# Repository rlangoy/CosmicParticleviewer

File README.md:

# Cosmic particle readout system overview

## Readout Hardware

Schematics and PCB layout is found inn the kicadv6 folder   \
Design files for the cover is found in the the CAD foldder 

## Project Content 
### alpideInterface
Microcontroller firmware source for [Arduino IDE 2.x](https://github.com/arduino/arduino-ide) \
&nbsp; parses JSON command and sends it to the ALPIDES \
&nbsp; More Info Available in the [README](/ArduinoV2/README.md) 

### KicadV6  
PCB Design files for [Kicadv6] (https://www.kicad.org/) \
&nbsp; More Info Available in the [README](/KicadV6/README.md) 

### CAD  
CAD Design files for PCB cover [Freecad v0.21] (https://www.freecad.org/) \
&nbsp; More Info Available in the [README](/CAD/README.md) 

### Python
Python ver 3.x Library and Examples for reading/accessing the Alpide OB Modules \
&nbsp; More Info Available in the [README](/Python/README.md)

### InfluxDB
InfluxDB 2.x Python3 script for inserting ALPIDE data into the daatabase and Script for building the Dashboard \
&nbsp; More Info Available in the [README](/InfluxDB/README.md)

## Getting started
- Transfer .u2f file to the RPI Pico
- Modify Serial port in plotAplideHitmap.py
  - Run [plotAplideHitmap.py](/Python/plotAplideHitmap.py) (python3 plotAplideHitmap.py )

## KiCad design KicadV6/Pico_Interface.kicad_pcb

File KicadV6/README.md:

# Kicad Files for Raspberry Pico (RP2040) interface to Outer Barrel Module
## PCB Layout. 
 
\
The Mounting holes is designed for 4M Screws \

## RP2040 Pinout 

## +3,3V Source Selection

## Fabrication
The PCB can be fabricated by uploading the gerber files (KicadV6\gerber\Pico_Interface.zip)  to a [PCB manufacurer](https://jlcpcb.com/) 

## Bil of Materials (BOM)

| Quantity | Reference(s) | Prod no             | Farnell order no | Description                                                |   |
|----------|--------------|---------------------|------------------|------------------------------------------------------------|---|
| 1        | C1           | T491A106K016AT      | 1457414          | T491A106K016AT CAP, 10µF, 16V, 10%, 1206, SMD              |   |
| 4        | J0-J3        | MC-254-12-00-ST-DIP | 2843528          | MC-254-12-00-ST-DIP CONNECTOR, HEADER, 12POS, 2ROW, 2.54MM |   |
| 1        | U2           | NCP1117ST33T3G      | 1652366          | NCP1117ST33T3G IC, LINEAR VOLTAGE REGULATOR                |   |
| 1        | U1           |                     |                  | Rasbperry Pi Pico                                          |   |

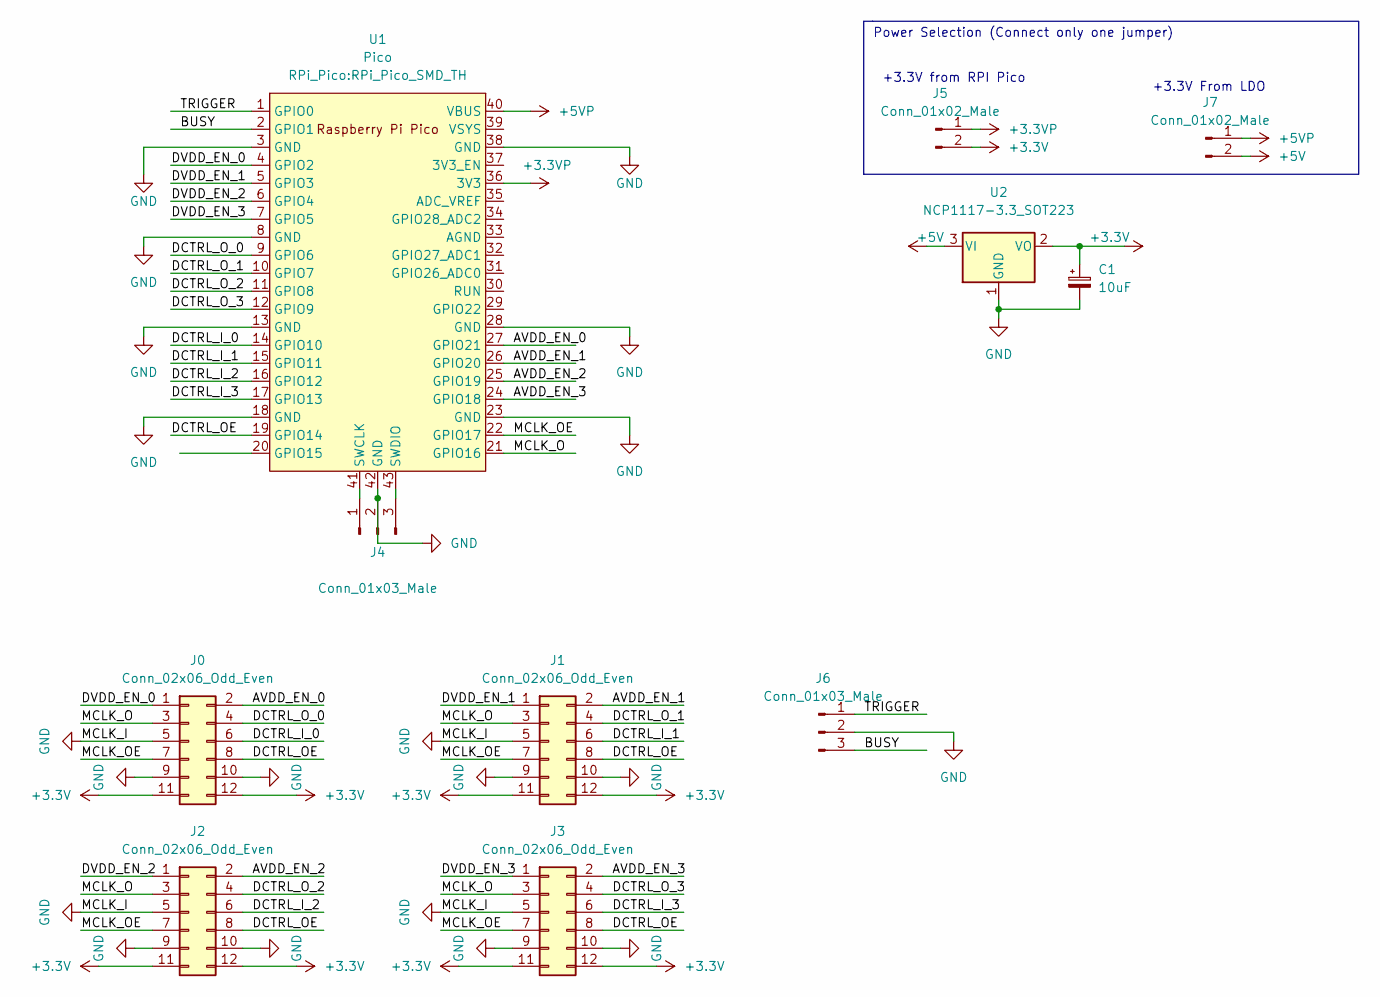
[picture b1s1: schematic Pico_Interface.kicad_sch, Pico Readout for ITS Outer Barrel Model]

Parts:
C1: 10uF; C_1206_3216Metric_Pad1.33x1.80mm_HandSolder
J0, J1, J2, J3: Conn_02x06_Odd_Even; IDC-Header_2x06_P2.54mm_Vertical
J4, J6: Conn_01x03_Male; PinHeader_1x03_P2.54mm_Vertical
J5, J7: Conn_01x02_Male; PinHeader_1x02_P2.54mm_Vertical
U1: Pico; RPi_Pico_SMD_TH
U2: NCP1117-3.3_SOT223; SOT-223-3_TabPin2

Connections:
+3.3V: C1.1, J0.11, J0.12, J1.11, J1.12, J2.11, J2.12, J3.11, J3.12, J5.2, U2.2 (VO)
+3.3VP: J5.1, U1.36 (3V3)
+5V: J7.2, U2.3 (VI)
+5VP: J7.1, U1.40 (VBUS)
/AVDD_EN_0: J0.2, U1.27 (GPIO21)
/AVDD_EN_1: J1.2, U1.26 (GPIO20)
/AVDD_EN_2: J2.2, U1.25 (GPIO19)
/AVDD_EN_3: J3.2, U1.24 (GPIO18)
/BUSY: J6.3, U1.2 (GPIO1)
/DCTRL_I_0: J0.6, U1.14 (GPIO10)
/DCTRL_I_1: J1.6, U1.15 (GPIO11)
/DCTRL_I_2: J2.6, U1.16 (GPIO12)
/DCTRL_I_3: J3.6, U1.17 (GPIO13)
/DCTRL_OE: J0.8, J1.8, J2.8, J3.8, U1.19 (GPIO14)
/DCTRL_O_0: J0.4, U1.9 (GPIO6)
/DCTRL_O_1: J1.4, U1.10 (GPIO7)
/DCTRL_O_2: J2.4, U1.11 (GPIO8)
/DCTRL_O_3: J3.4, U1.12 (GPIO9)
/DVDD_EN_0: J0.1, U1.4 (GPIO2)
/DVDD_EN_1: J1.1, U1.5 (GPIO3)
/DVDD_EN_2: J2.1, U1.6 (GPIO4)
/DVDD_EN_3: J3.1, U1.7 (GPIO5)
/MCLK_O: J0.3, J1.3, J2.3, J3.3, U1.21 (GPIO16)
/MCLK_OE: J0.7, J1.7, J2.7, J3.7, U1.22 (GPIO17)
/TRIGGER: J6.1, U1.1 (GPIO0)
GND: C1.2, J0.5, J0.9, J0.10, J1.5, J1.9, J1.10, J2.5, J2.9, J2.10, J3.5, J3.9, J3.10, J4.2, J6.2, U1.3 (GND), U1.8 (GND), U1.13 (GND), U1.18 (GND), U1.23 (GND), U1.28 (GND), U1.38 (GND), U1.42 (GND), U2.1 (GND)
unnamed: J4.1, U1.41 (SWCLK)
unnamed: J4.3, U1.43 (SWDIO)

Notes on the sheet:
Power Selection (Connect only one jumper)
+3.3V From LDO
+3.3V from RPI Pico

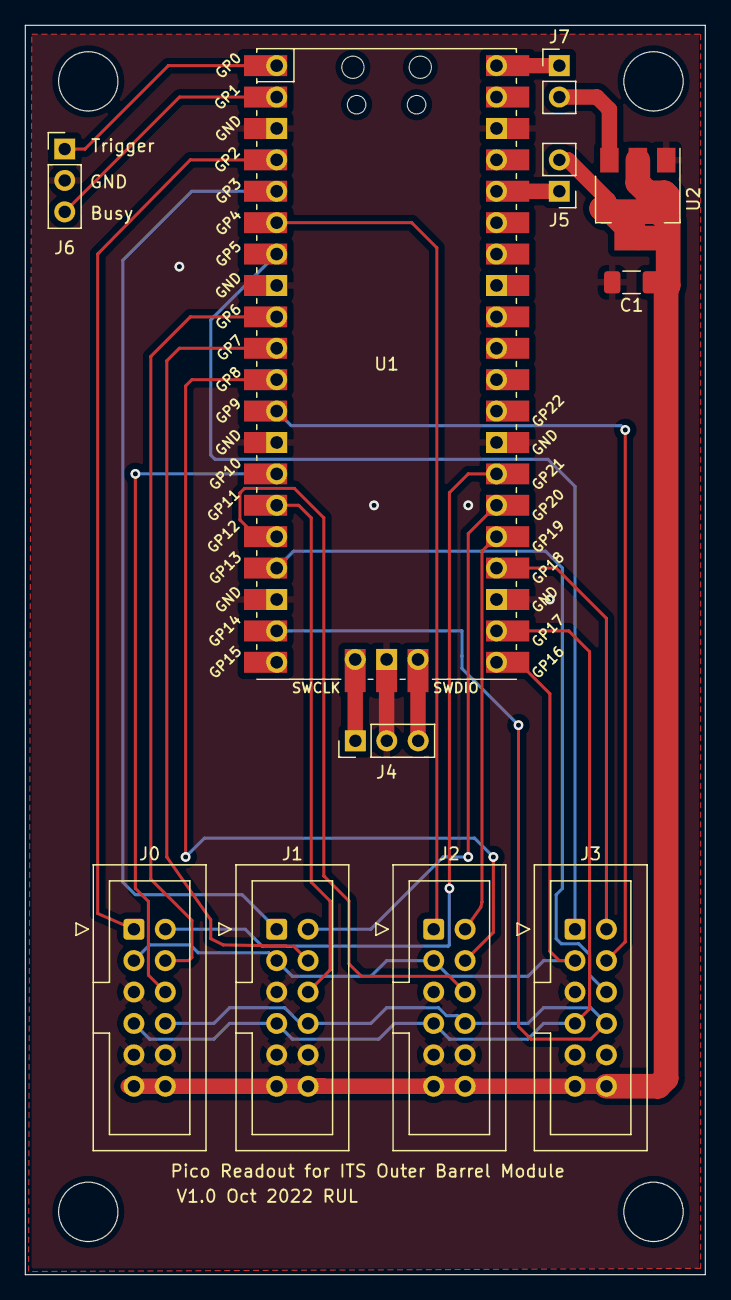
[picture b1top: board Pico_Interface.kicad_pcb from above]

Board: 2 copper layers, 55.0 x 101.1 mm, 11 parts (0 on the bottom side), 28 nets.

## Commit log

2022-10-19 Arduino IDEv2.0 RPI PICO Serial Interface for the ITS OB telescope
2022-10-19 RAW FIFO Data Containing ALPIDE Hits
2022-10-19 Library RPI Pico Serial <--> ALPIDE OB Module
2022-10-19 Example usage of Library RPI Pico Serial <--> ALPIDE OB Module
2022-10-19 RPI Pico interface
2022-10-20 Added 4 PMOD / IDC Connectors
2022-10-20 DRC Warning fix
2022-10-20 Cleanup
2022-10-20 Add Reset before sending trigger
2022-10-20 Bug Fix
2022-10-20 Started change of layout
2022-10-20 Added Trigger/Bussy and 3.3V LDO
2022-10-21 Added new Col to BOM (Farnell Order URL)
2022-10-21 BOM Update
2022-10-21 Added Title Block
2022-10-21 Kicad PCB Routed and ready for Production
2022-10-21 Fix Silk text
2022-10-22 Setting eanable export of all components into .setp (Pio Pico is only in wrl..)
2022-10-22 Added Images
2022-10-23 Add new file
2022-10-24 Added 3d Models and RPI Pico symbol & foothprint
2022-10-26 Update create SW masj
2022-10-27 Changed pinout to 4x RaddoutBoard
2022-10-27 Added more functionality
2022-10-27 Added functions for detecting always on pixels
2022-10-27 started on func filterOutDeadPix
2022-10-27 Added Simple Backplane
2022-10-27 Add img
2022-10-27 View Update
2022-10-28 Add board width bumper image
2022-10-28 Added USB Pocket
2022-10-28 added function getNewHits (removes always on-pix)
2022-10-31 Added Comments
2022-10-31 Arduino CLI install Instructions
2022-11-01 BugFix Send reset and not trigger on reset command
2022-11-01 Fix trigger sends Readout (RRU/TRU/DMU) reset before trigger
2022-11-02 Fix Cover fitting
2022-11-03 Added timeout if no new pix-data is avaliable
2022-11-04 Increase default strobelength and clk is always output
2022-11-06 InfluDB script to push data to DB
2022-11-06 InfluxDB Dashboard
2022-11-06 System block diagram
2022-11-06 Added img
2022-11-07 Added new img
